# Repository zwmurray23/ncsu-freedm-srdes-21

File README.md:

#  Open Source Modular Compute System for Real-Time Control and Data Acquisition

Researchers working on power electronic prototypes need specialized devices for signal conditioning and control. In the past, researchers have solved this problem by creating control devices for each of their projects. They often have to recreate common circuits, and single mistakes can lead to reworks of large and expensive boards. Our solution is a modular system that can be configured for use in different projects. We have developed an open-source compute/control device made of interchangeable cards that handle I/O, signal conditioning, data acquisition, and control. Researchers can further extend the functionality of the device by swapping in cards of their own design.

Sponsor: FREEDM Systems Center - Mark Nations, Dr. Richard Beddingfield
Team Members: Jacob Williams, Julia Germano, Zachary Murray

NCSU ECE 484 & 485  
Fall 2021 - Spring 2022
Senior Design Project 20

KiCAD 5 PCB designs: Backplane, DSP, FO and ADC

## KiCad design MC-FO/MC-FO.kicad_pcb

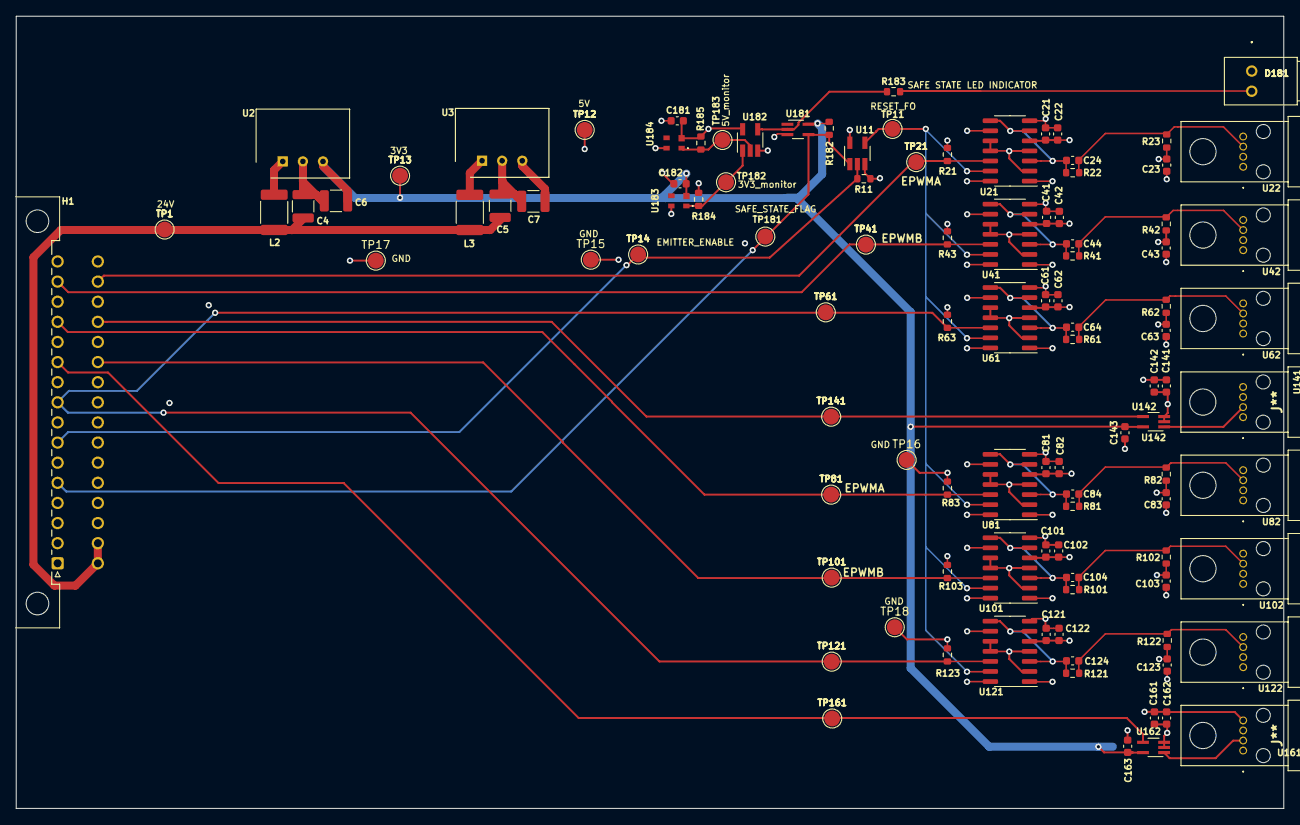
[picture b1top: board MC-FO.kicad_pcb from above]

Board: 4 copper layers, 160.0 x 100.0 mm, 106 parts (0 on the bottom side), 40 nets.

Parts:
C4, C5: 4.7 uF; C_1210_3225Metric
C6, C7: unpopulated; C_1210_3225Metric
C21, C23, C41, C43, C61, C63, C81, C83, C101, C103, C121, C123, C141, C143, C161, C163: 0.1 uF; C_0603_1608Metric
C22, C42, C62, C82, C102, C122, C142, C162: 10 uF; C_0603_1608Metric
C24, C44, C64, C84, C104, C124: 100 pF; C_0603_1608Metric
C181: 1 uF; C_0603_1608Metric
C182: 1 uF or unpop; C_0603_1608Metric
D181: WP1503CB_GD; WP1503CBGD
H1: 86094327313755E1LF
L2, L3: 3.9uH; L_1812_4532Metric_Pad1.30x3.40mm_HandSolder
R11, R21, R43, R63, R83, R103, R123, R182, R184, R185: 10K; R_0603_1608Metric
R22, R41, R61, R81, R101, R121: 150R; R_0603_1608Metric
R23, R42, R62, R82, R102, R122: 365R; R_0603_1608Metric
R183: 500R; R_0603_1608Metric
TP1, TP11, TP12, TP13, TP14, TP15, TP16, TP17, TP18, TP21, TP41, TP61, TP81, TP101, TP121, TP141, TP161, TP181, TP182, TP183: TestPoint; TestPoint_Pad_D2.0mm
U2: R-78E3.3-0.5; SIP3_11.6x8.5mm
U3: R-78E5.0-0.5; SIP3_11.6x8.5mm
U11, U182: 74LVCE1G08W5-7; SOT-23-5_HandSoldering
U21, U41, U61, U81, U101, U121: 74ACT08SCX; SOIC-14_3.9x8.7mm_P1.27mm
U22, U42, U62, U82, U102, U122: IFE98
U141, U161: IFD97
U142, U162: 74LVC1G02SE-7; SOT-353_SC-70-5_Handsoldering
U181: 74LVC1G07QDCKTQ1; SOT-353_SC-70-5_Handsoldering
U183: BU4831F-TR; BU4847F-TR
U184: BU4847F-TR

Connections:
24V: C4.1, C5.1, H1.17, H1.18, L2.1, L3.1, TP1.1
/Detector1/3V3: C6.1, C143.1, C163.1, C182.1, R182.1, TP13.1, U2.3, U142.5, U162.5, U181.5, U183.2
/Detector1/5V: C7.1, C21.1, C22.1, C23.1, C41.1, C42.1, C43.1, C61.1, C62.1, C63.1, C81.1, C82.1, C83.1, C101.1, C102.1, C103.1, C121.1, C122.1, C123.1, C141.1, C142.1, C161.1, C162.1, C181.1, R23.2, R42.2, R62.2, R82.2, R102.2, R122.2, R184.1, R185.1, TP12.1, U3.3, U11.5, U21.1, U21.5, U21.9, U21.14, U41.1, U41.5, U41.9, U41.14, U61.1, U61.5, U61.9, U61.14, U81.1, U81.5, U81.9, U81.14, U101.1, U101.5, U101.9, U101.14, U121.1, U121.5, U121.9, U121.14, U141.4, U161.4, U182.5, U184.2
/Emitter1/OUTPUT_ENABLE: TP11.1, U11.4, U21.13, U41.13, U61.13, U81.13, U101.13, U121.13
EMITTER_ENABLE: H1.7, R11.2, TP14.1, U11.2
EPWM1A: H1.31, R21.2, TP21.1, U21.12
EPWM1B: H1.15, R43.2, TP41.1, U41.12
EPWM2A: H1.13, R83.2, TP81.1, U81.12
EPWM2B: H1.27, R103.2, TP101.1, U101.12
GND: C4.2, C5.2, C6.2, C7.2, C21.2, C22.2, C23.2, C41.2, C42.2, C43.2, C61.2, C62.2, C63.2, C81.2, C82.2, C83.2, C101.2, C102.2, C103.2, C121.2, C122.2, C123.2, C141.2, C142.2, C143.2, C161.2, C162.2, C163.2, C181.2, C182.2, D181.1, H1.1, H1.2, H1.3, H1.4, H1.6, H1.8, H1.10, H1.12, H1.14, H1.16, H1.19, H1.20, H1.21, H1.22, H1.23, H1.24, H1.25, H1.26, H1.28, H1.30, H1.32, R11.1, R21.1, R43.1, R63.1, R83.1, R103.1, R123.1, TP15.1, TP16.1, TP17.1, TP18.1, U2.2, U3.2, U11.3, U21.7, U22.1, U22.2, U22.4, U41.7, U42.1, U42.2, U42.4, U61.7, U62.1, U62.2, U62.4, U81.7, U82.1, U82.2, U82.4, U101.7, U102.1, U102.2, U102.4, U121.7, U122.1, U122.2, U122.4, U141.1, U141.3, U142.2, U142.3, U161.1, U161.3, U162.2, U162.3, U181.3, U182.3, U183.4, U184.4
unnamed: C24.1, R22.1, U21.3, U21.6, U21.8
unnamed: C24.2, R22.2, R23.1, U22.3
unnamed: C44.1, R41.1, U41.3, U41.6, U41.8
unnamed: C44.2, R41.2, R42.1, U42.3
unnamed: C64.1, R61.1, U61.3, U61.6, U61.8
unnamed: C64.2, R61.2, R62.1, U62.3
unnamed: C84.1, R81.1, U81.3, U81.6, U81.8
unnamed: C84.2, R81.2, R82.1, U82.3
unnamed: C104.1, R101.1, U101.3, U101.6, U101.8
unnamed: C104.2, R101.2, R102.1, U102.3
unnamed: C124.1, R121.1, U121.3, U121.6, U121.8
unnamed: C124.2, R121.2, R122.1, U122.3
unnamed: D181.2, R183.1
unnamed: L2.2, U2.1
unnamed: L3.2, U3.1
unnamed: R183.2, U181.2, U182.4
unnamed: R184.2, TP182.1, U182.1, U183.1
unnamed: R185.2, TP183.1, U182.2, U184.1
unnamed: U21.2, U21.4, U21.10, U21.11
unnamed: U41.2, U41.4, U41.10, U41.11
unnamed: U61.2, U61.4, U61.10, U61.11
unnamed: U81.2, U81.4, U81.10, U81.11
unnamed: U101.2, U101.4, U101.10, U101.11
unnamed: U121.2, U121.4, U121.10, U121.11
unnamed: U141.2, U142.1
unnamed: U161.2, U162.1
RESET_Gate_Drivers_GPIO: H1.9, R63.2, R123.2, TP61.1, TP121.1, U61.12, U121.12
STATUS1: H1.29, TP141.1, U142.4
STATUS2: H1.11, TP161.1, U162.4
~SAFE_STATE_FLAG~: H1.5, R182.2, TP181.1, U11.1, U181.4

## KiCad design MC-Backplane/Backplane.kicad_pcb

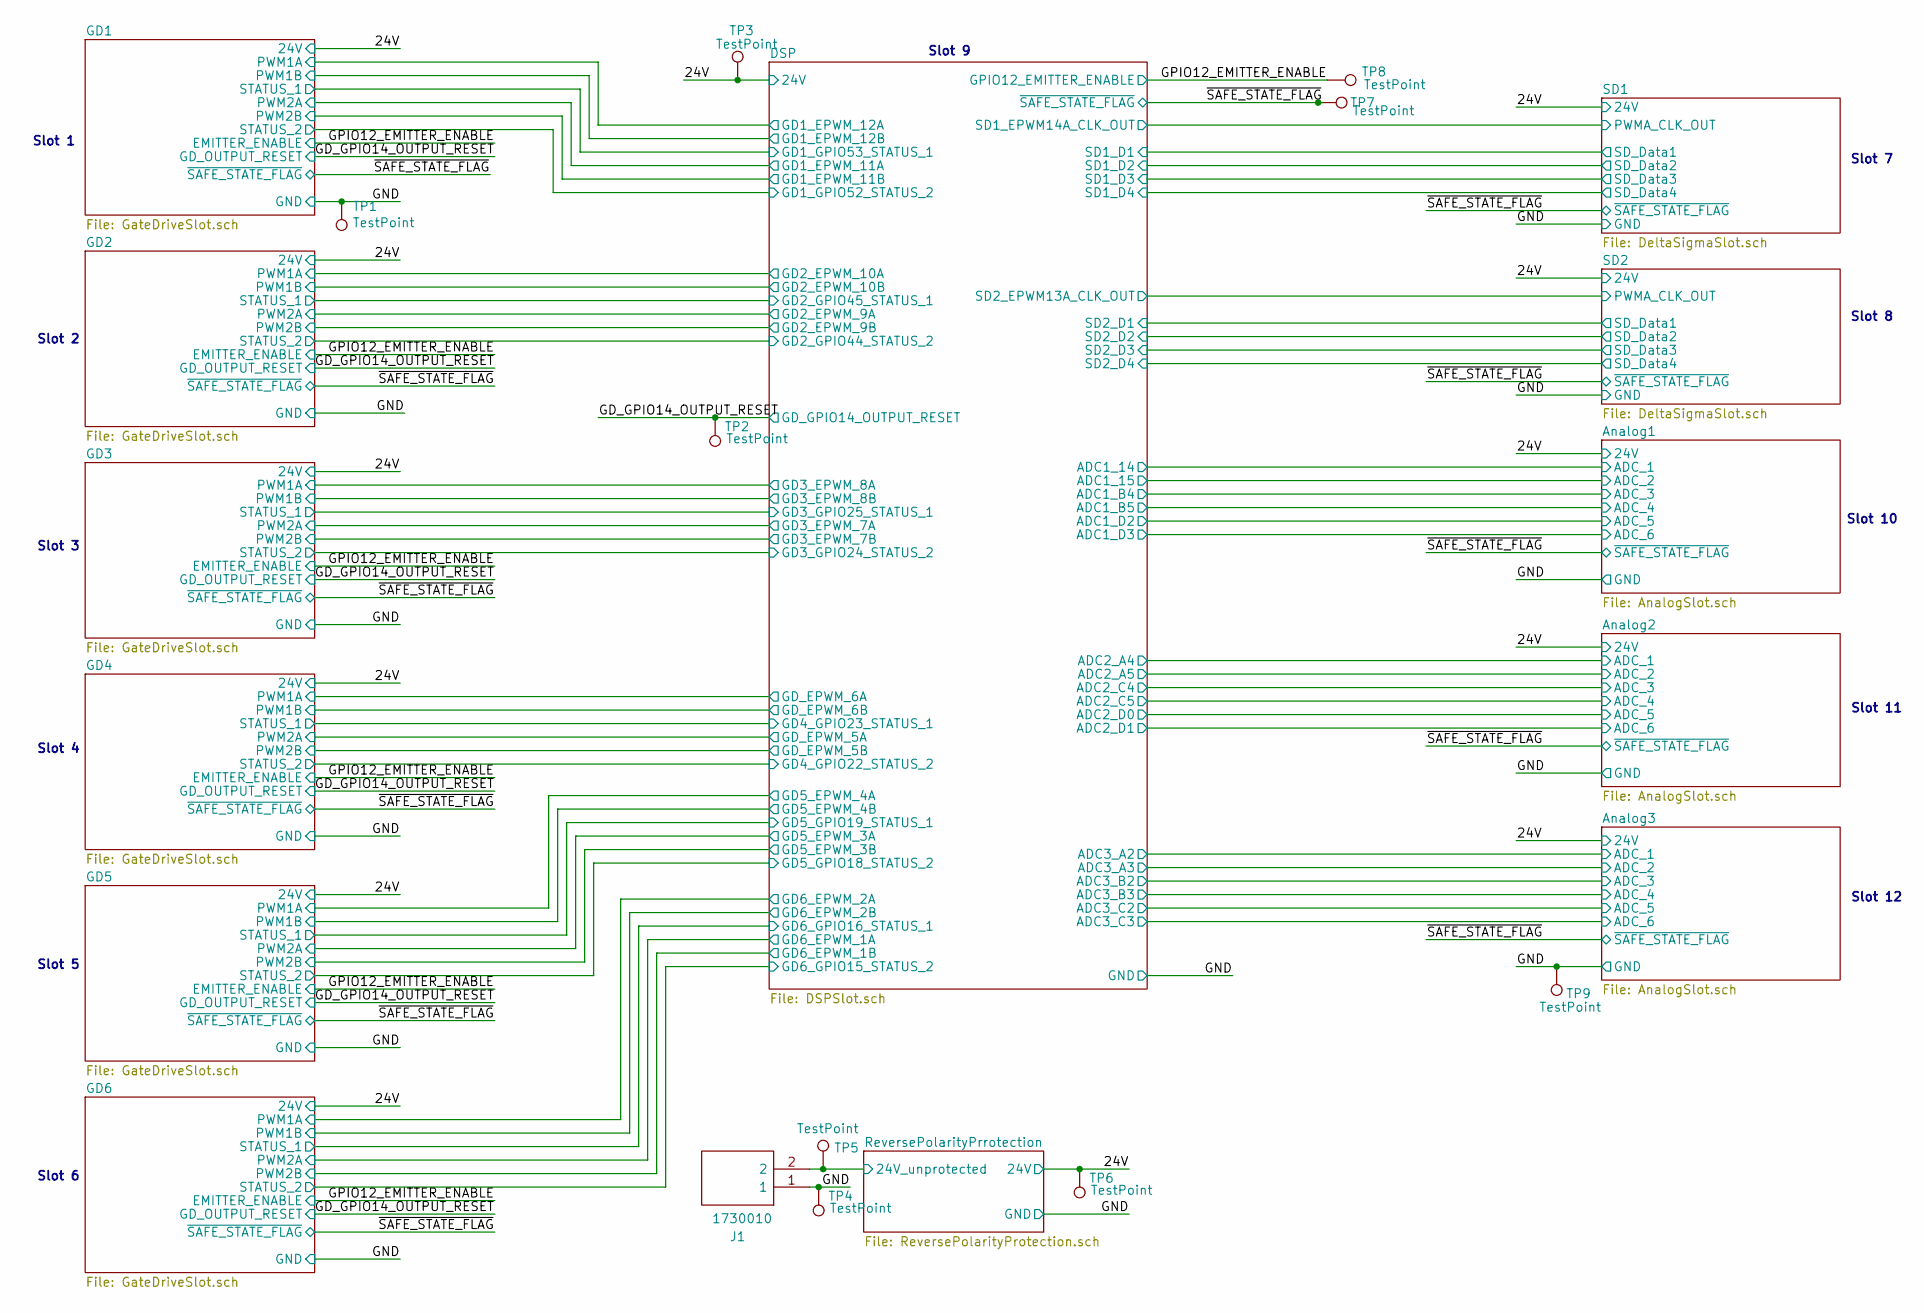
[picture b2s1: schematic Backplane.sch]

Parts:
J1: 1730010
TP1, TP2, TP3, TP4, TP5, TP6, TP7, TP8, TP9: TestPoint; TestPoint_Plated_Hole_D2.0mm

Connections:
/24V: TP3.1, TP6.1; also elsewhere on the board
/GD_GPIO14_OUTPUT_RESET: TP2.1; also elsewhere on the board
/GND: J1.1, TP1.1, TP4.1, TP9.1; also elsewhere on the board
/GPIO12_EMITTER_ENABLE: TP8.1; also elsewhere on the board
/ReversePolarityPrrotection/24V_unprotected: J1.2, TP5.1; also elsewhere on the board
/~SAFE_STATE_FLAG~: TP7.1; also elsewhere on the board

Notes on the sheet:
Slot 1
Slot 2
Slot 3
Slot 4
Slot 5
Slot 6
Slot 8
Slot 10
Slot 7
Slot 9
Slot 12
Slot 11

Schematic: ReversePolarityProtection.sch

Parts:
D1: BZX84C9V1-7-F; SOT-23_Handsoldering
R1: 3k; R_1206_3216Metric
U1: 64600001223
U2: SISS05DN-T1-GE3; Vishay_PowerPAK_1212-8_Single

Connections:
/24V: D1.3, U2.1, U2.2, U2.3; also elsewhere on the board
/GND: R1.2; also elsewhere on the board
/ReversePolarityPrrotection/24V_unprotected: U1.1 (in); also elsewhere on the board
unnamed: D1.1, R1.1, U2.4
unnamed: U1.2 (out), U2.5

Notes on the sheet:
Reverse Polarity Protection Circuit
RDS of PMOS needs to be really small like miliohms. Drain current needs to be larger than what the load requires. VDS needs to be larger than the source voltage by a significant amount. 24V so around 45V-60V. The Zener diode needs a voltage rating of just under VDS of the mosfet.
zener
fuse
there is a correction on this page. Originally the input of zener was parked as pin 2 which does not match the footprint. The output was marked as pin 1 which is actually the input.. THe PMOS also had issues. The pin numbers did not match the footprint. Ended up with the source connected to 3 diffe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

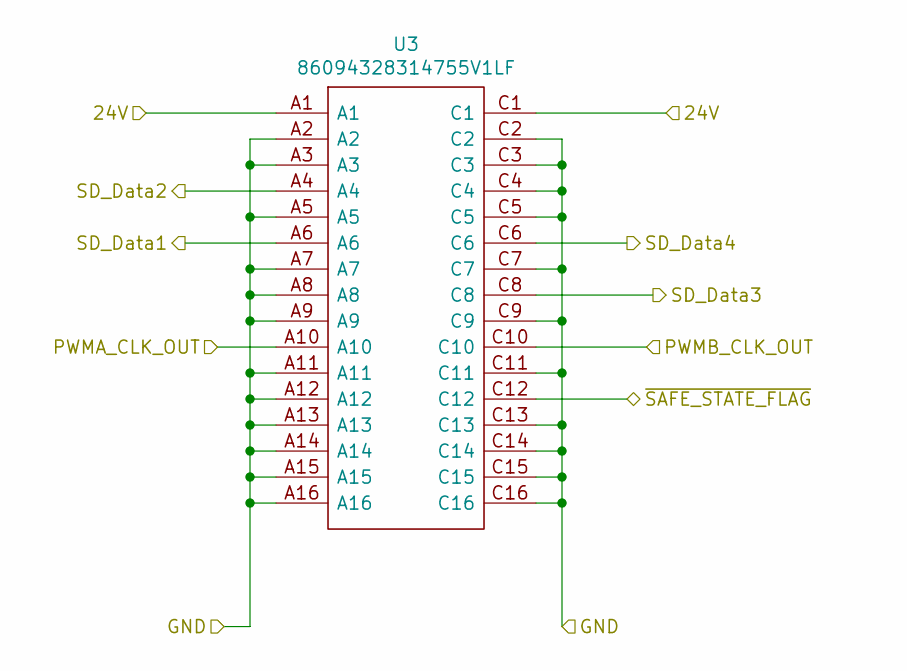
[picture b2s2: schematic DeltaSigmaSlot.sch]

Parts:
U3: 86094328314755V1LF; Manufacturer_Part_Number 86094328314755V1LF; Mouser Part Number 649-94328314755V1LF

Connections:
/24V: U3.A1, U3.C1; also elsewhere on the board
/DSP/SD1_D1: U3.A6; also elsewhere on the board
/DSP/SD1_D2: U3.A4; also elsewhere on the board
/DSP/SD1_D3: U3.C8; also elsewhere on the board
/DSP/SD1_D4: U3.C6; also elsewhere on the board
/GND: U3.A2, U3.A3, U3.A5, U3.A7, U3.A8, U3.A9, U3.A11, U3.A12, U3.A13, U3.A14, U3.A15, U3.A16, U3.C2, U3.C3, U3.C4, U3.C5, U3.C7, U3.C9, U3.C10, U3.C11, U3.C13, U3.C14, U3.C15, U3.C16; also elsewhere on the board
/SD1/PWMA_CLK_OUT: U3.A10; also elsewhere on the board
/~SAFE_STATE_FLAG~: U3.C12; also elsewhere on the board

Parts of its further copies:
U4: 86094328314755V1LF; Manufacturer_Part_Number 86094328314755V1LF; Mouser Part Number 649-94328314755V1LF

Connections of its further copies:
/24V: U4.A1, U4.C1; also elsewhere on the board
/DSP/SD2_D1: U4.A6; also elsewhere on the board
/DSP/SD2_D2: U4.A4; also elsewhere on the board
/DSP/SD2_D3: U4.C8; also elsewhere on the board
/DSP/SD2_D4: U4.C6; also elsewhere on the board
/GND: U4.A2, U4.A3, U4.A5, U4.A7, U4.A8, U4.A9, U4.A11, U4.A12, U4.A13, U4.A14, U4.A15, U4.A16, U4.C2, U4.C3, U4.C4, U4.C5, U4.C7, U4.C9, U4.C10, U4.C11, U4.C13, U4.C14, U4.C15, U4.C16; also elsewhere on the board
/SD2/PWMA_CLK_OUT: U4.A10; also elsewhere on the board
/~SAFE_STATE_FLAG~: U4.C12; also elsewhere on the board

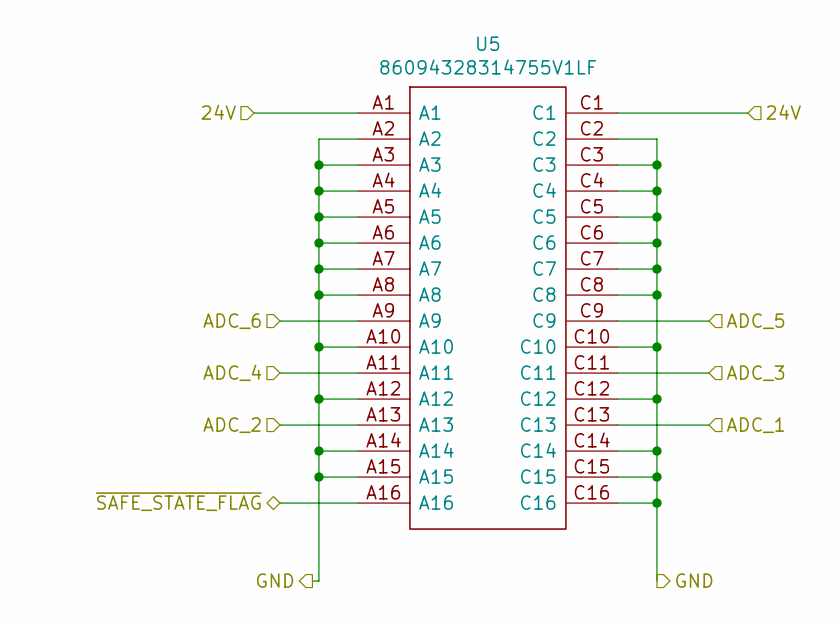
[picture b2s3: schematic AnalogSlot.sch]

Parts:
U5: 86094328314755V1LF; Manufacturer_Part_Number 86094328314755V1LF; Mouser Part Number 649-94328314755V1LF

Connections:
/24V: U5.A1, U5.C1; also elsewhere on the board
/DSP/ADC2_A4: U5.C13; also elsewhere on the board
/DSP/ADC2_A5: U5.A13; also elsewhere on the board
/DSP/ADC2_C4: U5.C11; also elsewhere on the board
/DSP/ADC2_C5: U5.A11; also elsewhere on the board
/DSP/ADC2_D0: U5.C9; also elsewhere on the board
/DSP/ADC2_D1: U5.A9; also elsewhere on the board
/GND: U5.A2, U5.A3, U5.A4, U5.A5, U5.A6, U5.A7, U5.A8, U5.A10, U5.A12, U5.A14, U5.A15, U5.C2, U5.C3, U5.C4, U5.C5, U5.C6, U5.C7, U5.C8, U5.C10, U5.C12, U5.C14, U5.C15, U5.C16; also elsewhere on the board
/~SAFE_STATE_FLAG~: U5.A16; also elsewhere on the board

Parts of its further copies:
U10, U11: 86094328314755V1LF; Manufacturer_Part_Number 86094328314755V1LF; Mouser Part Number 649-94328314755V1LF

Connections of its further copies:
/24V: U10.A1, U10.C1, U11.A1, U11.C1; also elsewhere on the board
/DSP/ADC1_14: U10.C13; also elsewhere on the board
/DSP/ADC1_15: U10.A13; also elsewhere on the board
/DSP/ADC1_B4: U10.C11; also elsewhere on the board
/DSP/ADC1_B5: U10.A11; also elsewhere on the board
/DSP/ADC1_D2: U10.C9; also elsewhere on the board
/DSP/ADC1_D3: U10.A9; also elsewhere on the board
/DSP/ADC3_A2: U11.C13; also elsewhere on the board
/DSP/ADC3_A3: U11.A13; also elsewhere on the board
/DSP/ADC3_B2: U11.C11; also elsewhere on the board
/DSP/ADC3_B3: U11.A11; also elsewhere on the board
/DSP/ADC3_C2: U11.C9; also elsewhere on the board
/DSP/ADC3_C3: U11.A9; also elsewhere on the board
/GND: U10.A2, U10.A3, U10.A4, U10.A5, U10.A6, U10.A7, U10.A8, U10.A10, U10.A12, U10.A14, U10.A15, U10.C2, U10.C3, U10.C4, U10.C5, U10.C6, U10.C7, U10.C8, U10.C10, U10.C12, U10.C14, U10.C15, U10.C16, U11.A2, U11.A3, U11.A4, U11.A5, U11.A6, U11.A7, U11.A8, U11.A10, U11.A12, U11.A14, U11.A15, U11.C2, U11.C3, U11.C4, U11.C5, U11.C6, U11.C7, U11.C8, U11.C10, U11.C12, U11.C14, U11.C15, U11.C16; also elsewhere on the board
/~SAFE_STATE_FLAG~: U10.A16, U11.A16; also elsewhere on the board

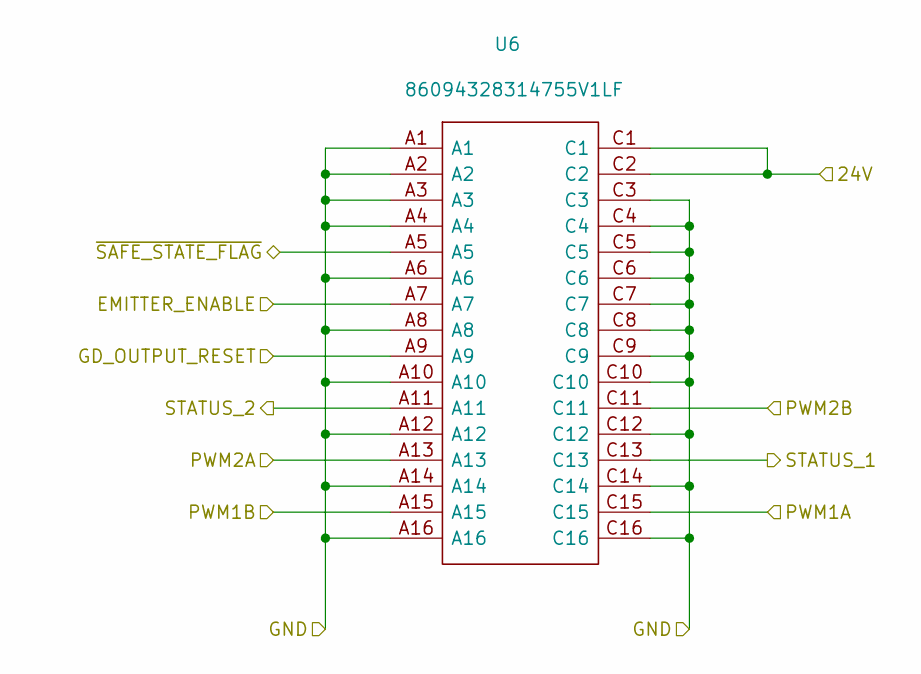
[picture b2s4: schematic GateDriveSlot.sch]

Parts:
U6: 86094328314755V1LF

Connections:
/24V: U6.C1, U6.C2; also elsewhere on the board
/DSP/GD1_EPWM_11A: U6.A13; also elsewhere on the board
/DSP/GD1_EPWM_11B: U6.C11; also elsewhere on the board
/DSP/GD1_EPWM_12A: U6.C15; also elsewhere on the board
/DSP/GD1_EPWM_12B: U6.A15; also elsewhere on the board
/DSP/GD1_GPIO52_STATUS_2: U6.A11; also elsewhere on the board
/DSP/GD1_GPIO53_STATUS_1: U6.C13; also elsewhere on the board
/GD_GPIO14_OUTPUT_RESET: U6.A9; also elsewhere on the board
/GND: U6.A1, U6.A2, U6.A3, U6.A4, U6.A6, U6.A8, U6.A10, U6.A12, U6.A14, U6.A16, U6.C3, U6.C4, U6.C5, U6.C6, U6.C7, U6.C8, U6.C9, U6.C10, U6.C12, U6.C14, U6.C16; also elsewhere on the board
/GPIO12_EMITTER_ENABLE: U6.A7; also elsewhere on the board
/~SAFE_STATE_FLAG~: U6.A5; also elsewhere on the board

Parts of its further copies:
U7, U8, U9, U13, U14: 86094328314755V1LF

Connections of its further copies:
/24V: U7.C1, U7.C2, U8.C1, U8.C2, U9.C1, U9.C2, U13.C1, U13.C2, U14.C1, U14.C2; also elsewhere on the board
/DSP/GD2_EPWM_9A: U13.A13; also elsewhere on the board
/DSP/GD2_EPWM_9B: U13.C11; also elsewhere on the board
/DSP/GD2_EPWM_10A: U13.C15; also elsewhere on the board
/DSP/GD2_EPWM_10B: U13.A15; also elsewhere on the board
/DSP/GD2_GPIO44_STATUS_2: U13.A11; also elsewhere on the board
/DSP/GD2_GPIO45_STATUS_1: U13.C13; also elsewhere on the board
/DSP/GD3_EPWM_7A: U14.A13; also elsewhere on the board
/DSP/GD3_EPWM_7B: U14.C11; also elsewhere on the board
/DSP/GD3_EPWM_8A: U14.C15; also elsewhere on the board
/DSP/GD3_EPWM_8B: U14.A15; also elsewhere on the board
/DSP/GD3_GPIO24_STATUS_2: U14.A11; also elsewhere on the board
/DSP/GD3_GPIO25_STATUS_1: U14.C13; also elsewhere on the board
/DSP/GD4_GPIO22_STATUS_2: U7.A11; also elsewhere on the board
/DSP/GD4_GPIO23_STATUS_1: U7.C13; also elsewhere on the board
/DSP/GD5_EPWM_3A: U9.A13; also elsewhere on the board
/DSP/GD5_EPWM_3B: U9.C11; also elsewhere on the board
/DSP/GD5_EPWM_4A: U9.C15; also elsewhere on the board
/DSP/GD5_EPWM_4B: U9.A15; also elsewhere on the board
/DSP/GD5_GPIO18_STATUS_2: U9.A11; also elsewhere on the board
/DSP/GD5_GPIO19_STATUS_1: U9.C13; also elsewhere on the board
/DSP/GD6_EPWM_1A: U8.A13; also elsewhere on the board
/DSP/GD6_EPWM_1B: U8.C11; also elsewhere on the board
/DSP/GD6_EPWM_2A: U8.C15; also elsewhere on the board
/DSP/GD6_EPWM_2B: U8.A15; also elsewhere on the board
/DSP/GD6_GPIO15_STATUS_2: U8.A11; also elsewhere on the board
/DSP/GD6_GPIO16_STATUS_1: U8.C13; also elsewhere on the board
/DSP/GD_EPWM_5A: U7.A13; also elsewhere on the board
/DSP/GD_EPWM_5B: U7.C11; also elsewhere on the board
/DSP/GD_EPWM_6A: U7.C15; also elsewhere on the board
/DSP/GD_EPWM_6B: U7.A15; also elsewhere on the board
/GD_GPIO14_OUTPUT_RESET: U7.A9, U8.A9, U9.A9, U13.A9, U14.A9; also elsewhere on the board
/GND: U7.A1, U7.A2, U7.A3, U7.A4, U7.A6, U7.A8, U7.A10, U7.A12, U7.A14, U7.A16, U7.C3, U7.C4, U7.C5, U7.C6, U7.C7, U7.C8, U7.C9, U7.C10, U7.C12, U7.C14, U7.C16, U8.A1, U8.A2, U8.A3, U8.A4, U8.A6, U8.A8, U8.A10, U8.A12, U8.A14, U8.A16, U8.C3, U8.C4, U8.C5, U8.C6, U8.C7, U8.C8, U8.C9, U8.C10, U8.C12, U8.C14, U8.C16, U9.A1, U9.A2, U9.A3, U9.A4, U9.A6, U9.A8, U9.A10, U9.A12, U9.A14, U9.A16, U9.C3, U9.C4, U9.C5, U9.C6, U9.C7, U9.C8, U9.C9, U9.C10, U9.C12, U9.C14, U9.C16, U13.A1, U13.A2, U13.A3, U13.A4, U13.A6, U13.A8, U13.A10, U13.A12, U13.A14, U13.A16, U13.C3, U13.C4, U13.C5, U13.C6, U13.C7, U13.C8, U13.C9, U13.C10, U13.C12, U13.C14, U13.C16, U14.A1, U14.A2, U14.A3, U14.A4, U14.A6, U14.A8, U14.A10, U14.A12, U14.A14, U14.A16, U14.C3, U14.C4, U14.C5, U14.C6, U14.C7, U14.C8, U14.C9, U14.C10, U14.C12, U14.C14, U14.C16; also elsewhere on the board
/GPIO12_EMITTER_ENABLE: U7.A7, U8.A7, U9.A7, U13.A7, U14.A7; also elsewhere on the board
/~SAFE_STATE_FLAG~: U7.A5, U8.A5, U9.A5, U13.A5, U14.A5; also elsewhere on the board

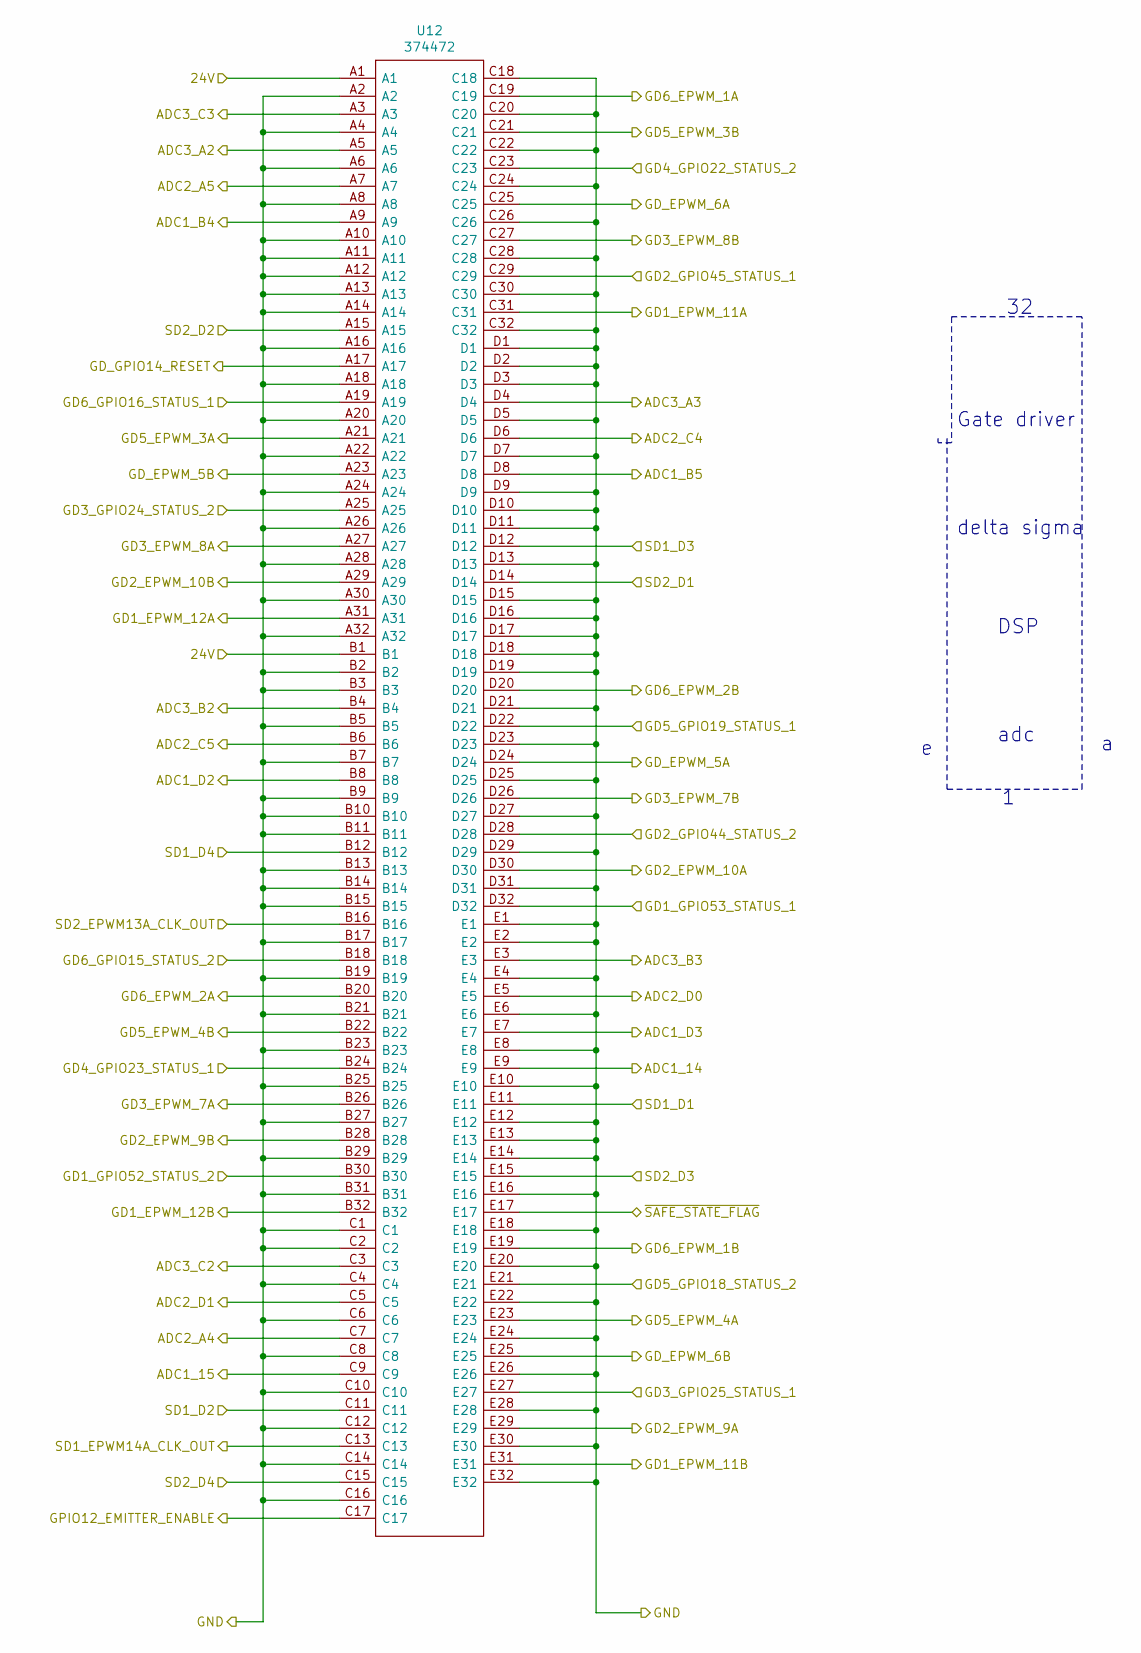
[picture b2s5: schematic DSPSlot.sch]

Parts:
U12: 374472; Manufacturer_Part_Number 374472; Mouser Part Number 305-374472

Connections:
/24V: U12.A1, U12.B1; also elsewhere on the board
/DSP/ADC1_14: U12.E9; also elsewhere on the board
/DSP/ADC1_15: U12.C9; also elsewhere on the board
/DSP/ADC1_B4: U12.A9; also elsewhere on the board
/DSP/ADC1_B5: U12.D8; also elsewhere on the board
/DSP/ADC1_D2: U12.B8; also elsewhere on the board
/DSP/ADC1_D3: U12.E7; also elsewhere on the board
/DSP/ADC2_A4: U12.C7; also elsewhere on the board
/DSP/ADC2_A5: U12.A7; also elsewhere on the board
/DSP/ADC2_C4: U12.D6; also elsewhere on the board
/DSP/ADC2_C5: U12.B6; also elsewhere on the board
/DSP/ADC2_D0: U12.E5; also elsewhere on the board
/DSP/ADC2_D1: U12.C5; also elsewhere on the board
/DSP/ADC3_A2: U12.A5; also elsewhere on the board
/DSP/ADC3_A3: U12.D4; also elsewhere on the board
/DSP/ADC3_B2: U12.B4; also elsewhere on the board
/DSP/ADC3_B3: U12.E3; also elsewhere on the board
/DSP/ADC3_C2: U12.C3; also elsewhere on the board
/DSP/ADC3_C3: U12.A3; also elsewhere on the board
/DSP/GD1_EPWM_11A: U12.C31; also elsewhere on the board
/DSP/GD1_EPWM_11B: U12.E31; also elsewhere on the board
/DSP/GD1_EPWM_12A: U12.A31; also elsewhere on the board
/DSP/GD1_EPWM_12B: U12.B32; also elsewhere on the board
/DSP/GD1_GPIO52_STATUS_2: U12.B30; also elsewhere on the board
/DSP/GD1_GPIO53_STATUS_1: U12.D32; also elsewhere on the board
/DSP/GD2_EPWM_9A: U12.E29; also elsewhere on the board
/DSP/GD2_EPWM_9B: U12.B28; also elsewhere on the board
/DSP/GD2_EPWM_10A: U12.D30; also elsewhere on the board
/DSP/GD2_EPWM_10B: U12.A29; also elsewhere on the board
/DSP/GD2_GPIO44_STATUS_2: U12.D28; also elsewhere on the board
/DSP/GD2_GPIO45_STATUS_1: U12.C29; also elsewhere on the board
/DSP/GD3_EPWM_7A: U12.B26; also elsewhere on the board
/DSP/GD3_EPWM_7B: U12.D26; also elsewhere on the board
/DSP/GD3_EPWM_8A: U12.A27; also elsewhere on the board
/DSP/GD3_EPWM_8B: U12.C27; also elsewhere on the board
/DSP/GD3_GPIO24_STATUS_2: U12.A25; also elsewhere on the board
/DSP/GD3_GPIO25_STATUS_1: U12.E27; also elsewhere on the board
/DSP/GD4_GPIO22_STATUS_2: U12.C23; also elsewhere on the board
/DSP/GD4_GPIO23_STATUS_1: U12.B24; also elsewhere on the board
/DSP/GD5_EPWM_3A: U12.A21; also elsewhere on the board
/DSP/GD5_EPWM_3B: U12.C21; also elsewhere on the board
/DSP/GD5_EPWM_4A: U12.E23; also elsewhere on the board
/DSP/GD5_EPWM_4B: U12.B22; also elsewhere on the board
/DSP/GD5_GPIO18_STATUS_2: U12.E21; also elsewhere on the board
/DSP/GD5_GPIO19_STATUS_1: U12.D22; also elsewhere on the board
/DSP/GD6_EPWM_1A: U12.C19; also elsewhere on the board
/DSP/GD6_EPWM_1B: U12.E19; also elsewhere on the board
/DSP/GD6_EPWM_2A: U12.B20; also elsewhere on the board
/DSP/GD6_EPWM_2B: U12.D20; also elsewhere on the board
/DSP/GD6_GPIO15_STATUS_2: U12.B18; also elsewhere on the board
/DSP/GD6_GPIO16_STATUS_1: U12.A19; also elsewhere on the board
/DSP/GD_EPWM_5A: U12.D24; also elsewhere on the board
/DSP/GD_EPWM_5B: U12.A23; also elsewhere on the board
/DSP/GD_EPWM_6A: U12.C25; also elsewhere on the board
/DSP/GD_EPWM_6B: U12.E25; also elsewhere on the board
/DSP/SD1_D1: U12.E11; also elsewhere on the board
/DSP/SD1_D2: U12.C11; also elsewhere on the board
/DSP/SD1_D3: U12.D12; also elsewhere on the board
/DSP/SD1_D4: U12.B12; also elsewhere on the board
/DSP/SD2_D1: U12.D14; also elsewhere on the board
/DSP/SD2_D2: U12.A15; also elsewhere on the board
/DSP/SD2_D3: U12.E15; also elsewhere on the board
/DSP/SD2_D4: U12.C15; also elsewhere on the board
/GD_GPIO14_OUTPUT_RESET: U12.A17; also elsewhere on the board
/GND: U12.A2, U12.A4, U12.A6, U12.A8, U12.A10, U12.A11, U12.A12, U12.A13, U12.A14, U12.A16, U12.A18, U12.A20, U12.A22, U12.A24, U12.A26, U12.A28, U12.A30, U12.A32, U12.B2, U12.B3, U12.B5, U12.B7, U12.B9, U12.B10, U12.B11, U12.B13, U12.B14, U12.B15, U12.B17, U12.B19, U12.B21, U12.B23, U12.B25, U12.B27, U12.B29, U12.B31, U12.C1, U12.C2, U12.C4, U12.C6, U12.C8, U12.C10, U12.C12, U12.C14, U12.C16, U12.C18, U12.C20, U12.C22, U12.C24, U12.C26, U12.C28, U12.C30, U12.C32, U12.D1, U12.D2, U12.D3, U12.D5, U12.D7, U12.D9, U12.D10, U12.D11, U12.D13, U12.D15, U12.D16, U12.D17, U12.D18, U12.D19, U12.D21, U12.D23, U12.D25, U12.D27, U12.D29, U12.D31, U12.E1, U12.E2, U12.E4, U12.E6, U12.E8, U12.E10, U12.E12, U12.E13, U12.E14, U12.E16, U12.E18, U12.E20, U12.E22, U12.E24, U12.E26, U12.E28, U12.E30, U12.E32; also elsewhere on the board
/GPIO12_EMITTER_ENABLE: U12.C17; also elsewhere on the board
/SD1/PWMA_CLK_OUT: U12.C13; also elsewhere on the board
/SD2/PWMA_CLK_OUT: U12.B16; also elsewhere on the board
/~SAFE_STATE_FLAG~: U12.E17; also elsewhere on the board

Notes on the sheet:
adc
DSP
delta sigma
Gate driver

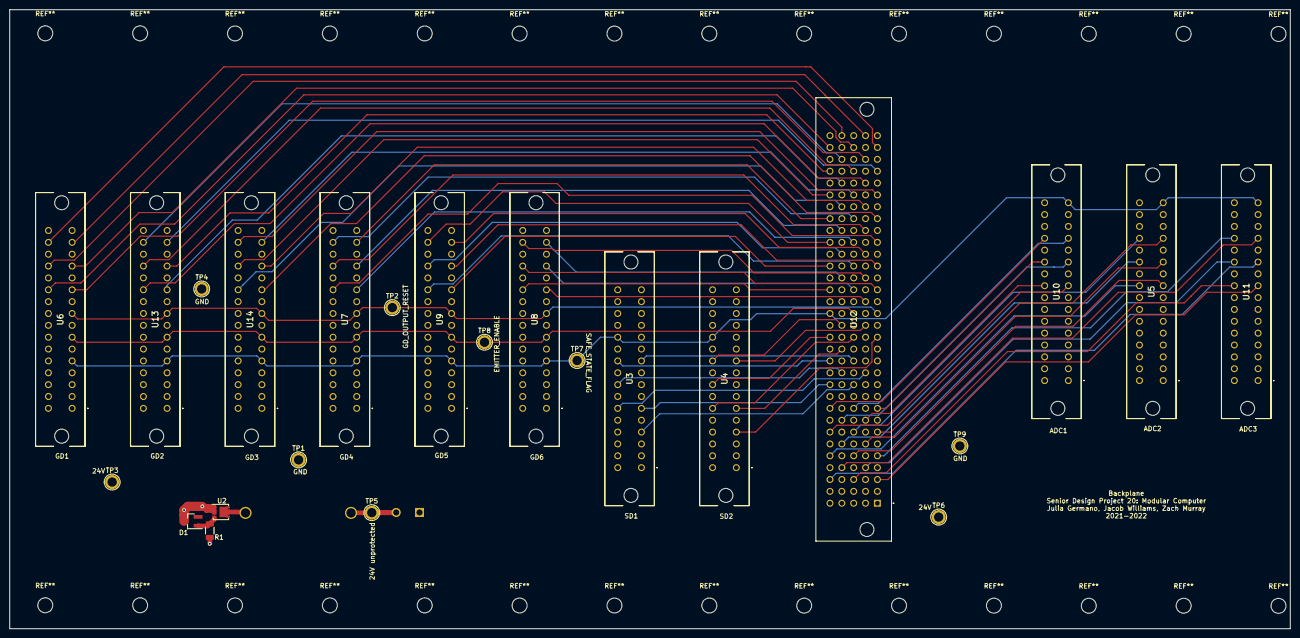
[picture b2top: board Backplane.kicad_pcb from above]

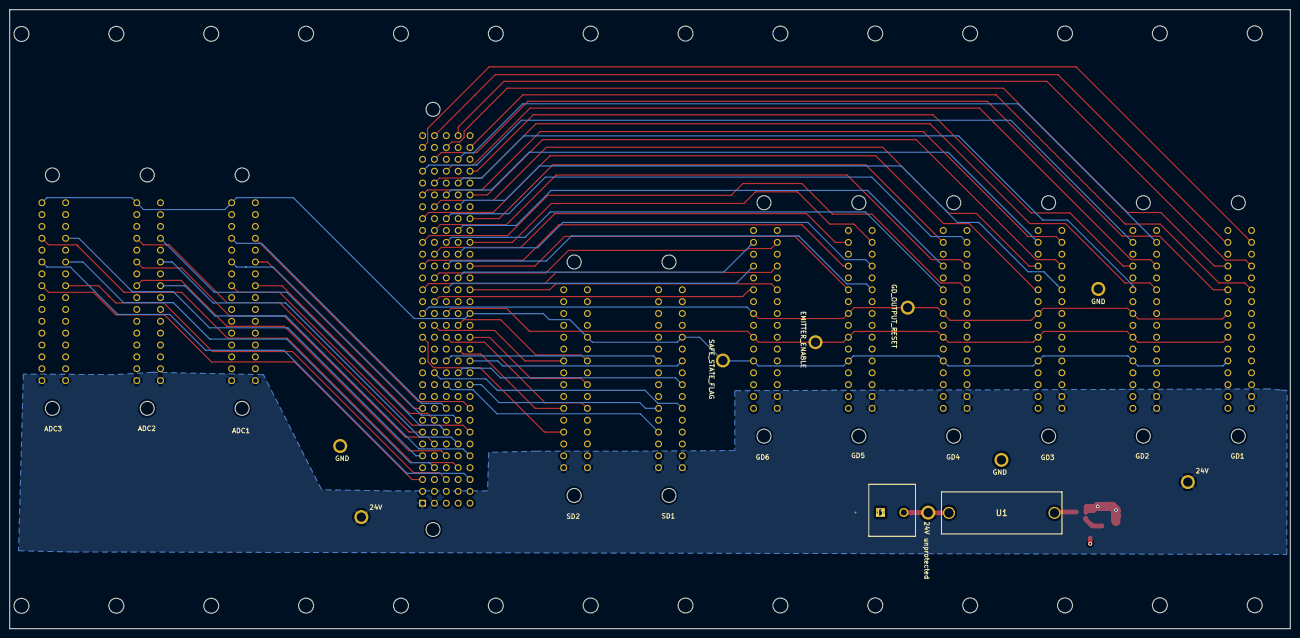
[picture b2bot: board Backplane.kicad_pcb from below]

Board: 4 copper layers, 274.3 x 132.6 mm, 26 parts (2 on the bottom side), 72 nets.
